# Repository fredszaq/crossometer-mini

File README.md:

# crossometer-mini

This repo contains the design files for the crossometer-mini device, an open hardware GPS/altimeter/variometer using the [crossometer-firmware](https://github.com/fredszaq/crossometer-firmware).

Provided are the Kicad files for the PCB and the Freecad files for the enclosure and clip.

Taking a look at open [issues](https://github.com/fredszaq/crossometer-mini/issues) may be a good idea if you intent do build a crossometer-mini for yourself.

Have a look at the [releases](https://github.com/fredszaq/crossometer-mini/releases) page to get gerber files and STLs.

crossometer-mini is licenced under the CERN Open Hardware Licence Version 2 - Strongly Reciprocal

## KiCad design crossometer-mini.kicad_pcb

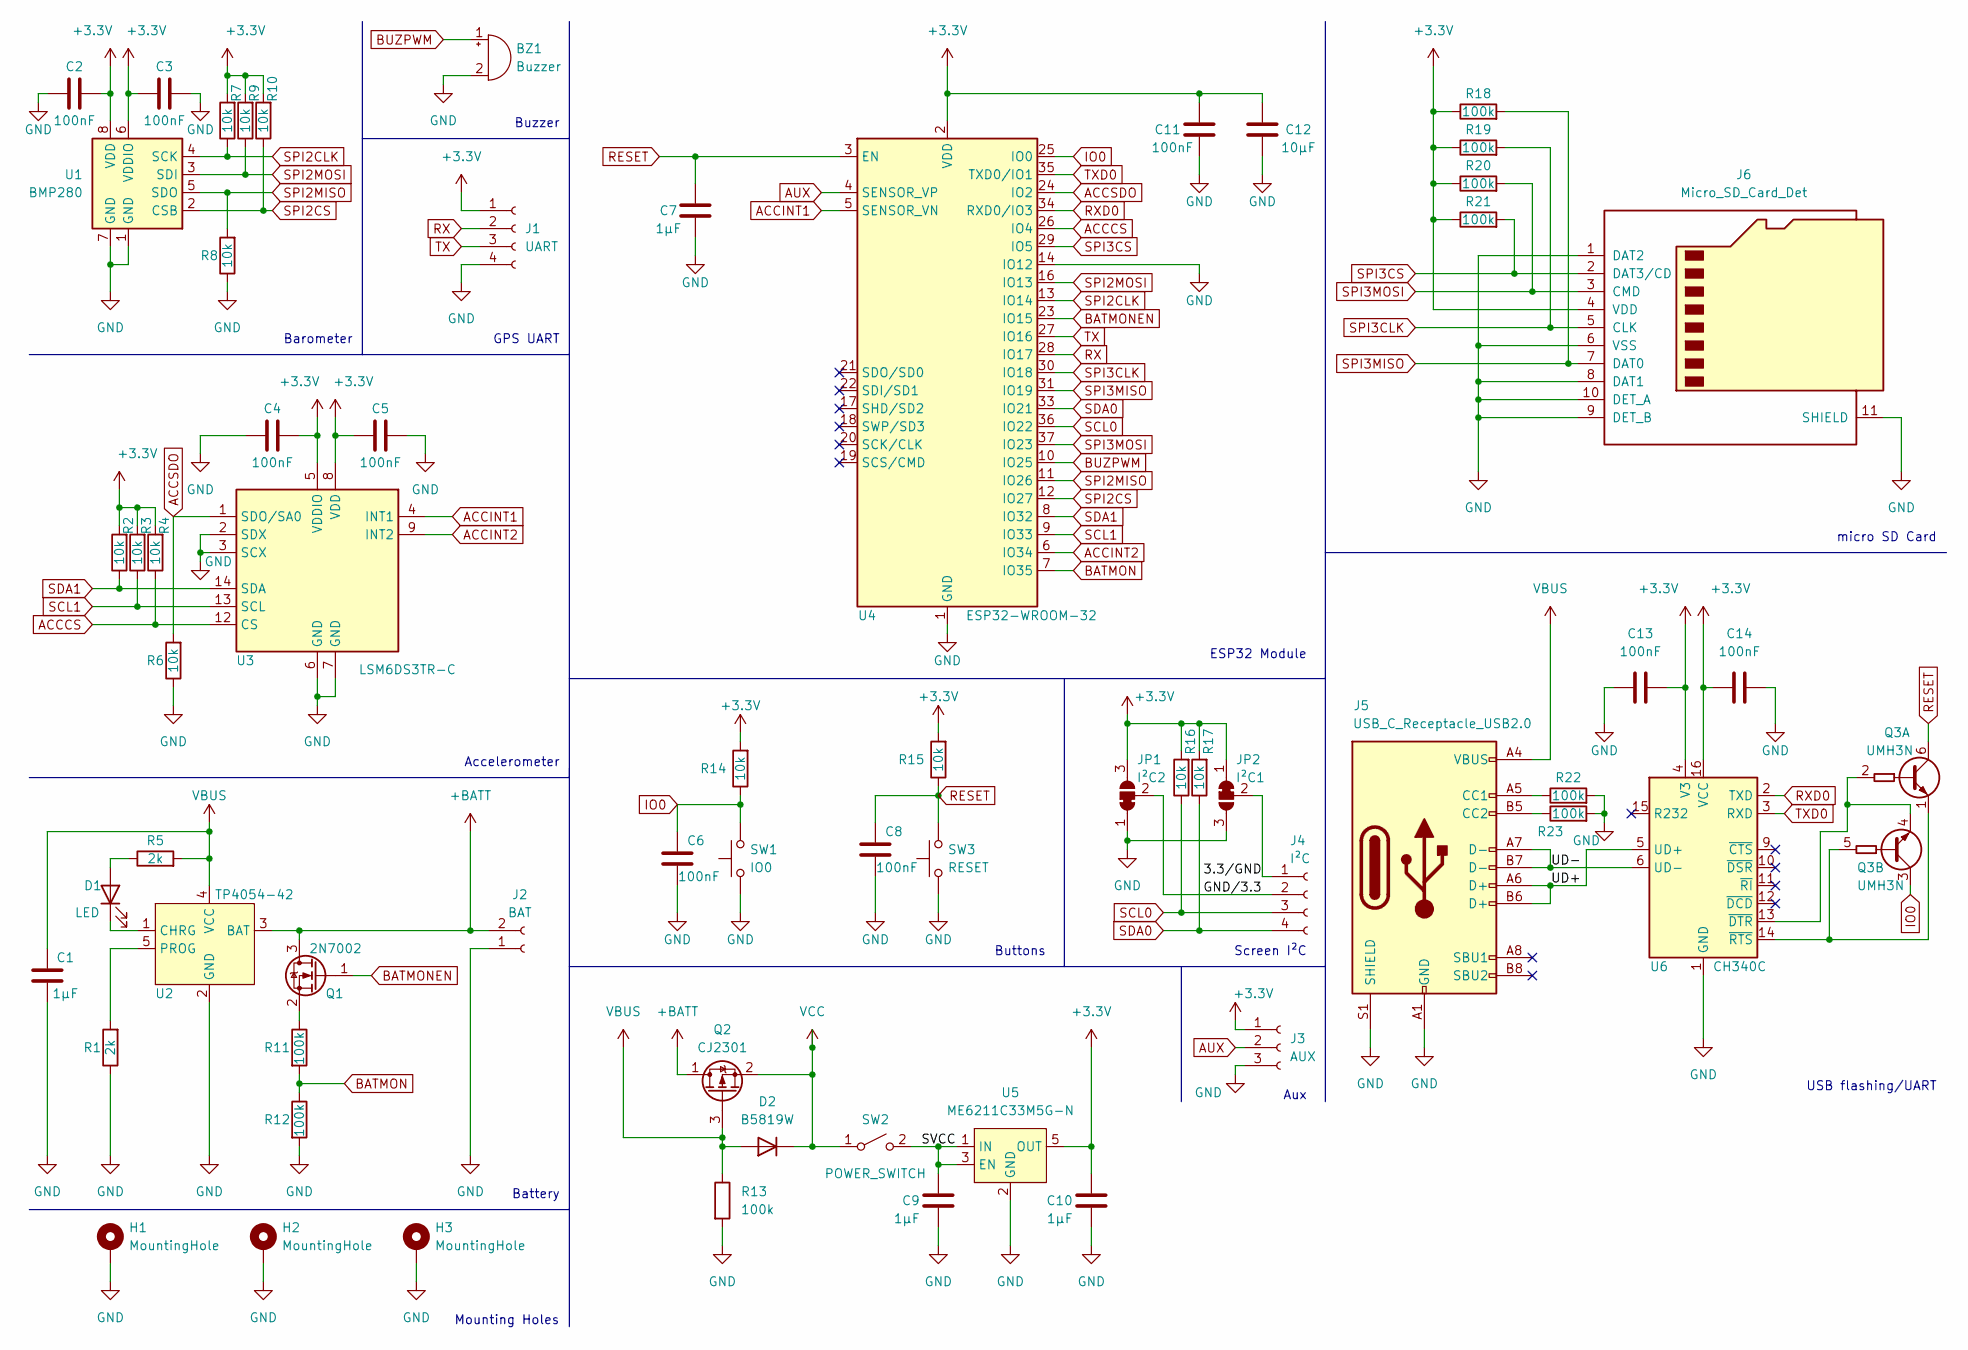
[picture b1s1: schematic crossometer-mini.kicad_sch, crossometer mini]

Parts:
BZ1: Buzzer; Buzzer_12x9.5RM7.6
C1, C7, C9, C10: 1µF; C_0402_1005Metric_Pad0.74x0.62mm_HandSolder; LCSC C52923
C2, C3, C4, C5, C6, C8, C11, C13, C14: 100nF; C_0402_1005Metric_Pad0.74x0.62mm_HandSolder; LCSC C1525
C12: 10µF; C_0402_1005Metric_Pad0.74x0.62mm_HandSolder; LCSC C15525
D1: LED; LED_0402_1005Metric_Pad0.77x0.64mm_HandSolder; LCSC C965790
D2: B5819W; D_SOD-123; LCSC C8598
H1, H2, H3: MountingHole; MountingHole_2.7mm_M2.5_ISO7380_Pad
J1: UART; PinHeader_1x04_P2.54mm_Vertical
J2: BAT; JST_PH_S2B-PH-SM4-TB_1x02-1MP_P2.00mm_Horizontal
J3: AUX; PinHeader_1x03_P2.54mm_Vertical
J4: I²C; PinHeader_1x04_P2.54mm_Vertical
J5: USB_C_Receptacle_USB2.0; USB_C_Receptacle_XKB_U262-16XN-4BVC11; LCSC C319148
J6: Micro_SD_Card_Det; microSD_HC_Molex_104031-0811; LCSC C585350
JP1: I²C2; SolderJumper-3_P1.3mm_Bridged12_RoundedPad1.0x1.5mm_NumberL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
JP2: I²C1; SolderJumper-3_P1.3mm_Bridged12_RoundedPad1.0x1.5mm_NumberL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
Q1: 2N7002; SOT-23; LCSC C8545
Q2: CJ2301; SOT-23; LCSC C2910170
Q3: UMH3N; SOT-363_SC-70-6; LCSC C62892
R1, R5: 2k; R_0402_1005Metric_Pad0.72x0.64mm_HandSolder; LCSC C4109
R2, R3, R4, R6, R7, R8, R9, R10, R14, R15, R16, R17: 10k; R_0402_1005Metric_Pad0.72x0.64mm_HandSolder; LCSC C25744
R11, R12, R13, R18, R19, R20, R21, R22, R23: 100k; R_0402_1005Metric_Pad0.72x0.64mm_HandSolder; LCSC C25741
SW1: IO0; SW_Push_SPST_NO_Alps_SKRK; LCSC C115357
SW2: POWER_SWITCH; SW_SPDT_PCM12; LCSC C221841
SW3: RESET; SW_Push_SPST_NO_Alps_SKRK; LCSC C115357
U1: BMP280; Bosch_LGA-8_2x2.5mm_P0.65mm_ClockwisePinNumbering; LCSC C83291
U2: TP4054-42; SOT-23-5_HandSoldering; LCSC C32574
U3: LSM6DS3TR-C; Bosch_LGA-14_3x2.5mm_P0.5mm; LCSC C967633
U4: ESP32-WROOM-32; LCSC C82899
U5: ME6211C33M5G-N; SOT-23-5_HandSoldering; LCSC C82942
U6: CH340C; SOIC-16_3.9x9.9mm_P1.27mm; LCSC C84681

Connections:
+3V3: C2.1, C3.2, C4.1, C5.2, C10.1, C11.1, C12.1, C13.2, C14.1, J1.1, J3.1, J6.4 (VDD), JP1.3 (B), JP2.1 (A), R2.2, R3.2, R4.2, R7.2, R9.2, R10.2, R14.2, R15.2, R16.2, R17.2, R18.1, R19.1, R20.1, R21.1, U1.6 (VDDIO), U1.8 (VDD), U3.5 (VDDIO), U3.8 (VDD), U4.2 (VDD), U5.5 (OUT), U6.4 (V3), U6.16 (VCC)
+BATT: J2.2, Q1.3 (D), Q2.1 (D), U2.3 (BAT)
/3.3/GND: J4.1, JP2.2 (C)
/GND/3.3: J4.2, JP1.2 (C)
/SVCC: C9.1, SW2.2 (B), U5.1 (IN), U5.3 (EN)
/UD+: J5.A6 (D+), J5.B6 (D+), U6.5 (UD+)
/UD-: J5.A7 (D-), J5.B7 (D-), U6.6 (UD-)
ACCCS: R4.1, U3.12 (CS), U4.26 (IO4)
ACCINT1: U3.4 (INT1), U4.5 (SENSOR_VN)
ACCINT2: U3.9 (INT2), U4.6 (IO34)
ACCSDO: R6.2, U3.1 (SDO/SA0), U4.24 (IO2)
AUX: J3.2, U4.4 (SENSOR_VP)
BATMON: R11.2, R12.1, U4.7 (IO35)
BATMONEN: Q1.1 (G), U4.23 (IO15)
BUZPWM: BZ1.1 (-), U4.10 (IO25)
GND: BZ1.2 (+), C1.1, C2.2, C3.1, C4.2, C5.1, C6.2, C7.2, C8.2, C9.2, C10.2, C11.2, C12.2, C13.1, C14.2, H1.1, H2.1, H3.1, J1.4, J2.1, J3.3, J5.A1 (GND), J5.A12 (GND), J5.B1 (GND), J5.B12 (GND), J5.S1 (SHIELD), J6.1 (DAT2), J6.6 (VSS), J6.8 (DAT1), J6.9 (DET_B), J6.10 (DET_A), J6.11 (SHIELD), JP1.1 (A), JP2.3 (B), R1.1, R6.1, R8.1, R12.2, R13.2, R22.2, R23.2, SW1.1, SW3.1, U1.1 (GND), U1.7 (GND), U2.2 (GND), U3.2 (SDX), U3.3 (SCX), U3.6 (GND), U3.7 (GND), U4.1 (GND), U4.14 (IO12), U4.15 (GND), U4.38 (GND), U4.39 (GND), U5.2 (GND), U6.1 (GND)
IO0: C6.1, Q3.3 (C2), R14.1, SW1.2, U4.25 (IO0)
unnamed: D1.1 (K), U2.1 (CHRG)
unnamed: D1.2 (A), R5.1
unnamed: J5.A5 (CC1), R22.1
unnamed: J5.B5 (CC2), R23.1
unnamed: Q1.2 (S), R11.1
unnamed: Q3.1 (E1), Q3.5 (B2), U6.14 (~RTS)
unnamed: Q3.2 (B1), Q3.4 (E2), U6.13 (~DTR)
unnamed: R1.2, U2.5 (PROG)
RESET: C7.1, C8.1, Q3.6 (C1), R15.1, SW3.2, U4.3 (EN)
RX: J1.2, U4.28 (IO17)
RXD0: U4.34 (RXD0/IO3), U6.2 (TXD)
SCL0: J4.3, R16.1, U4.36 (IO22)
SCL1: R3.1, U3.13 (SCL), U4.9 (IO33)
SDA0: J4.4, R17.1, U4.33 (IO21)
SDA1: R2.1, U3.14 (SDA), U4.8 (IO32)
SPI2CLK: R7.1, U1.4 (SCK), U4.13 (IO14)
SPI2CS: R10.1, U1.2 (CSB), U4.12 (IO27)
SPI2MISO: R8.2, U1.5 (SDO), U4.11 (IO26)
SPI2MOSI: R9.1, U1.3 (SDI), U4.16 (IO13)
SPI3CLK: J6.5 (CLK), R19.2, U4.30 (IO18)
SPI3CS: J6.2 (DAT3/CD), R21.2, U4.29 (IO5)
SPI3MISO: J6.7 (DAT0), R18.2, U4.31 (IO19)
SPI3MOSI: J6.3 (CMD), R20.2, U4.37 (IO23)
TX: J1.3, U4.27 (IO16)
TXD0: U4.35 (TXD0/IO1), U6.3 (RXD)
VBUS: C1.2, D2.2 (A), J5.A4 (VBUS), J5.A9 (VBUS), J5.B4 (VBUS), J5.B9 (VBUS), Q2.3 (G), R5.2, R13.1, U2.4 (VCC)
VCC: D2.1 (K), Q2.2 (S), SW2.1 (A)

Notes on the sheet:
USB flashing/UART
micro SD Card
ESP32 Module
Accelerometer
Buttons
Buzzer
Mounting Holes
Battery
Screen I²C
GPS UART
Aux
Barometer

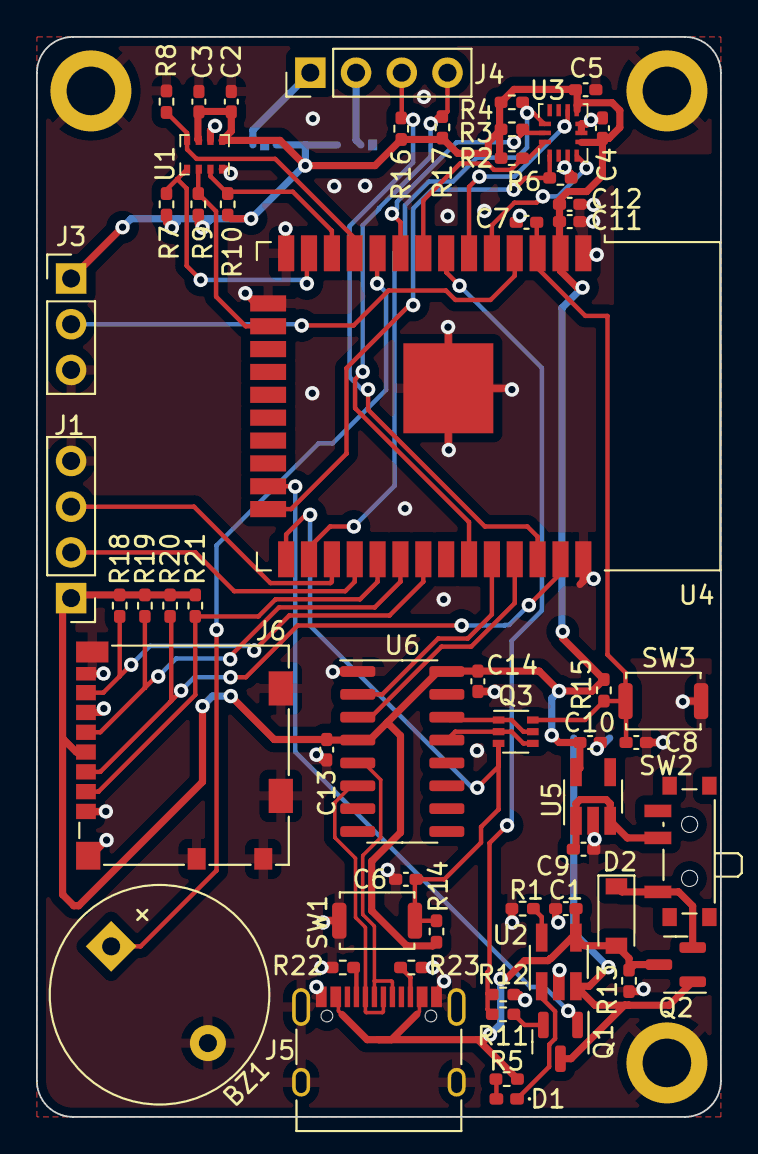
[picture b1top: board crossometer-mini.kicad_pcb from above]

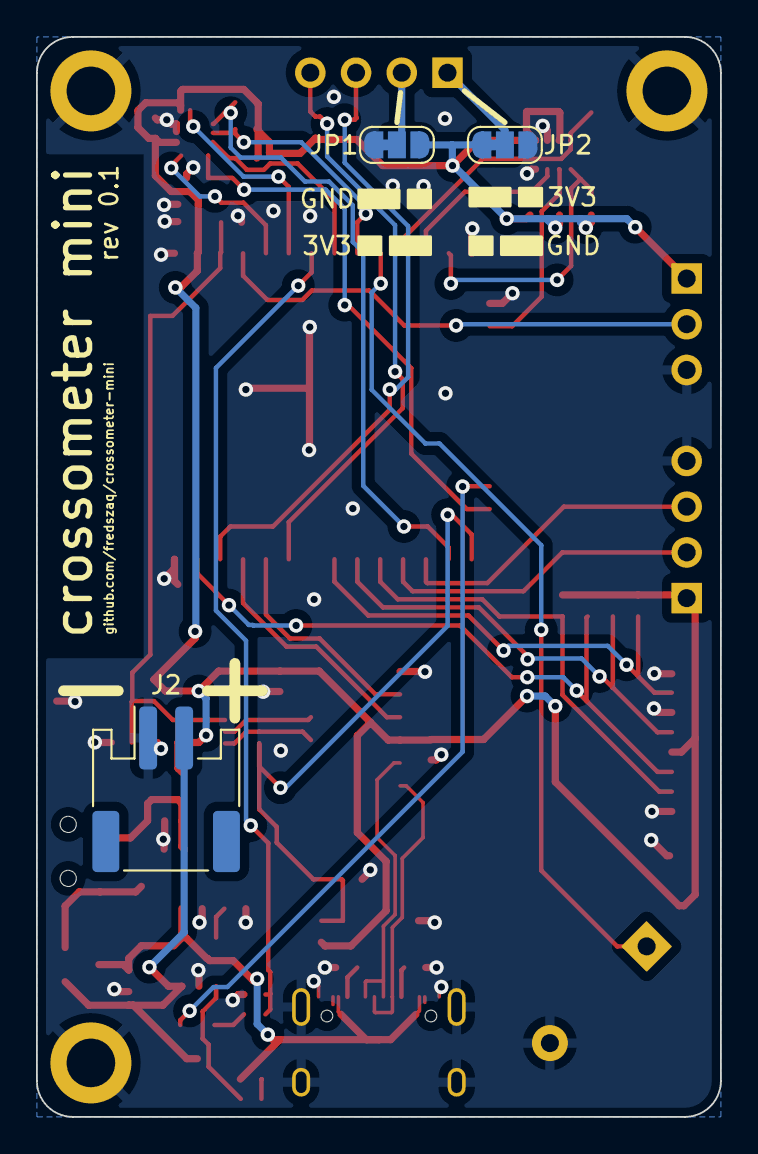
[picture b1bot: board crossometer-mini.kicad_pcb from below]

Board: 2 copper layers, 38.0 x 60.0 mm, 63 parts (3 on the bottom side), 44 nets.

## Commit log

2022-08-10 add LCSC field to schematic
2022-08-27 add 3d design files
2024-08-26 add readme
2024-08-26 kicad 8 changes
2024-08-26 add pcb 3d render to readme
2024-08-26 better readme
2024-08-26 add licence
